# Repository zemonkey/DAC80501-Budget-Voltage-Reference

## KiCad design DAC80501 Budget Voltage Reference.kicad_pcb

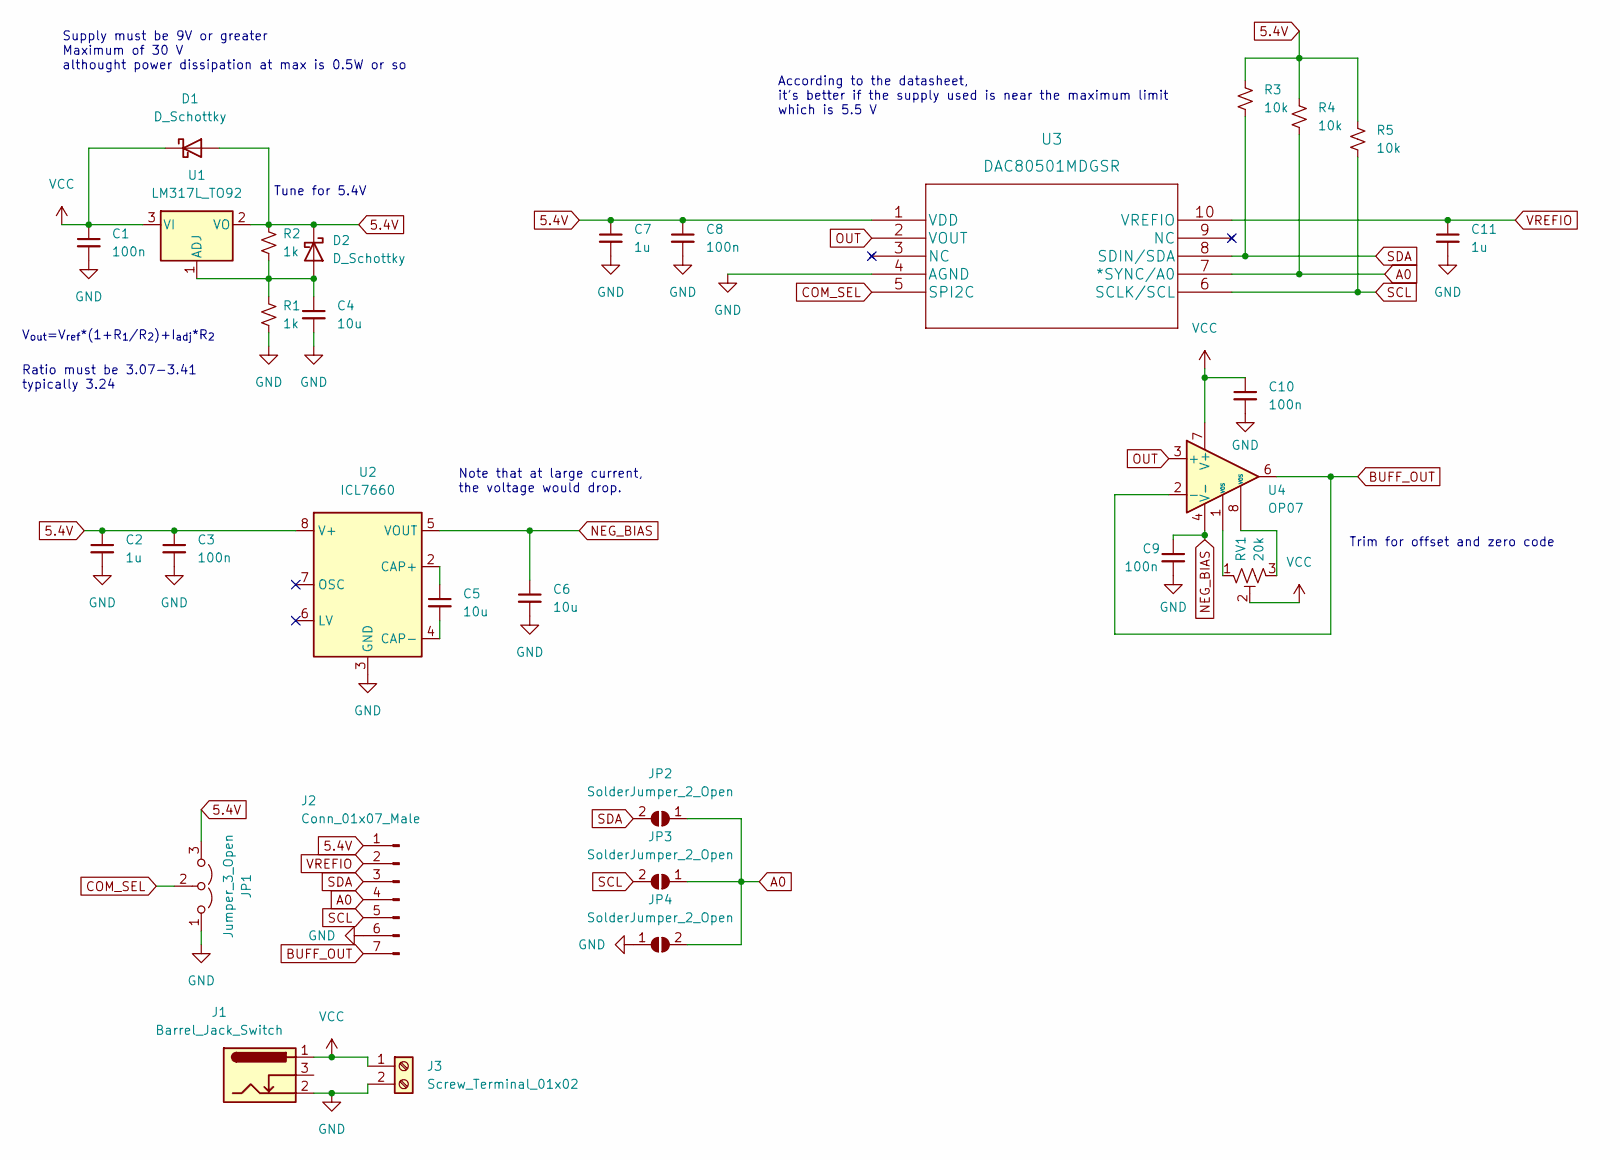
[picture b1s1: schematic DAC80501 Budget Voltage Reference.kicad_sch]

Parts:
C1, C3, C8, C9, C10: 100n; C_0805_2012Metric_Pad1.18x1.45mm_HandSolder
C2, C7, C11: 1u; C_0805_2012Metric_Pad1.18x1.45mm_HandSolder
C4, C5, C6: 10u; C_0805_2012Metric_Pad1.18x1.45mm_HandSolder
D1, D2: D_Schottky; D_SOD-123
J1: Barrel_Jack_Switch; BarrelJack_AE
J2: Conn_01x07_Male; PinHeader_1x07_P2.54mm_Vertical
J3: Screw_Terminal_01x02; TerminalBlock_RND_205-00001_1x02_P5.00mm_Horizontal
JP1: Jumper_3_Open; PinHeader_1x03_P2.54mm_Vertical
JP2, JP3, JP4: SolderJumper_2_Open; SolderJumper-2_P1.3mm_Open_TrianglePad1.0x1.5mm
R1, R2: 1k; R_0805_2012Metric_Pad1.20x1.40mm_HandSolder
R3, R4, R5: 10k; R_0805_2012Metric_Pad1.20x1.40mm_HandSolder
RV1: 20k; Potentiometer_Bourns_3296Y_Vertical
U1: LM317L_TO92; TO-92_Inline_Wide
U2: ICL7660; SOIC-8_3.9x4.9mm_P1.27mm
U3: DAC80501MDGSR; VSSOP-10_3x3mm_P0.5mm
U4: OP07; SOIC-8_3.9x4.9mm_P1.27mm

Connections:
5.4V: C2.1, C3.1, C7.1, C8.1, D1.2 (A), D2.1 (K), J2.1, JP1.3 (B), R2.1, R3.1, R4.1, R5.1, U1.2 (VO), U2.8 (V+), U3.1 (VDD)
A0: J2.4, JP2.1 (A), JP3.1 (A), JP4.2 (B), R4.2, U3.7 (*SYNC/A0)
BUFF_OUT: J2.7, U4.2 (-), U4.6
COM_SEL: JP1.2 (C), U3.5 (SPI2C)
GND: C1.2, C2.2, C3.2, C4.2, C6.2, C7.2, C8.2, C9.2, C10.2, C11.2, J1.2, J2.6, J3.2, JP1.1 (A), JP4.1 (A), R1.2, U2.3 (GND), U3.4 (AGND)
NEG_BIAS: C6.1, C9.1, U2.5 (VOUT), U4.4 (V-)
unnamed: C4.1, D2.2 (A), R1.1, R2.2, U1.1 (ADJ)
unnamed: C5.1, U2.2 (CAP+)
unnamed: C5.2, U2.4 (CAP-)
unnamed 9: RV1.1, U4.1 (VOS); also elsewhere on the board
unnamed 10: RV1.3, U4.8 (VOS); also elsewhere on the board
OUT: U3.2 (VOUT), U4.3 (+)
SCL: J2.5, JP3.2 (B), R5.2, U3.6 (SCLK/SCL)
SDA: J2.3, JP2.2 (B), R3.2, U3.8 (SDIN/SDA)
VCC: C1.1, C10.1, D1.1 (K), J1.1, J3.1, RV1.2, U1.3 (VI), U4.7 (V+); also elsewhere on the board
VREFIO: C11.1, J2.2, U3.10 (VREFIO)

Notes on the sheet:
Supply must be 9V or greater Maximum of 30 V althought power dissipation at max is 0.5W or so
Ratio must be 3.07-3.41 typically 3.24
Trim for offset and zero code
Tune for 5.4V
Note that at large current, the voltage would drop.
According to the datasheet, it's better if the supply used is near the maximum limit which is 5.5 V
V_{out}=V_{ref}*(1+R_{1}/R_{2})+I_{adj}*R_{2}

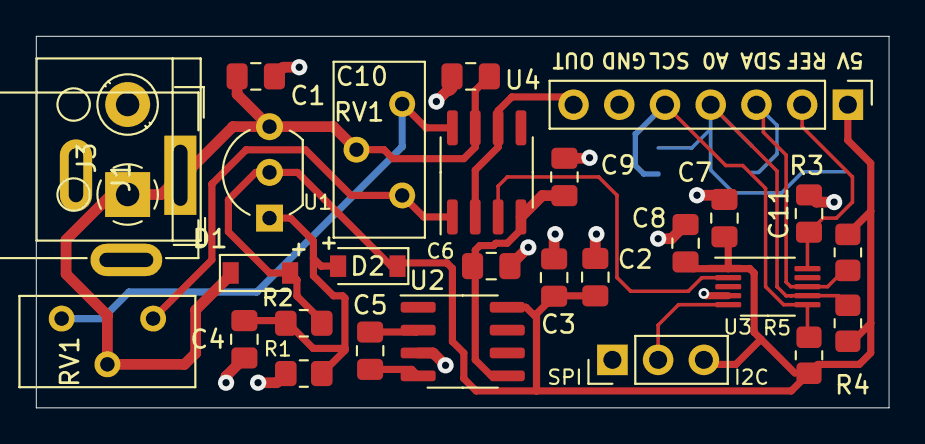
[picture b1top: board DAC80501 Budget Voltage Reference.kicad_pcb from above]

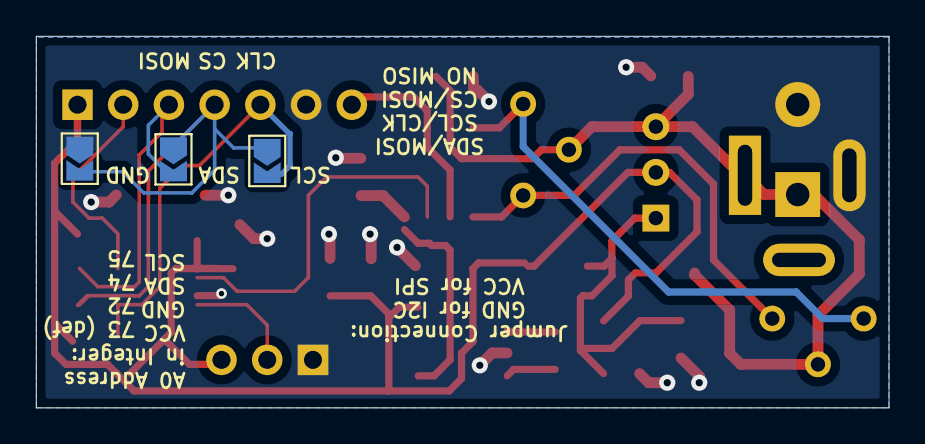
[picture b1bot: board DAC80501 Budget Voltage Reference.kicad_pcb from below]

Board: 2 copper layers, 47.4 x 20.6 mm, 31 parts (3 on the bottom side), 16 nets.

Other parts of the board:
RV1#2: 20k; Potentiometer_Bourns_3296Y_Vertical

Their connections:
unnamed 9: RV1#2.1; also elsewhere on the board
unnamed 10: RV1#2.3; also elsewhere on the board
VCC: RV1#2.2; also elsewhere on the board
